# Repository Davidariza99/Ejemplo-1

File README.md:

# Proyecto embebidos (Pet_Sitting)

## Integrantes:

- David Ariza
- Andres Unibio
- Sharem Alonso

## Descripción:
Vigilante y cuidador de mascotas en casa, permite al usuario interactuar con su mascota a la distacia.

## Justificación: 
Se ha presentado un aumento significativo de la adopción de mascotas durante la pandemia, a medida que las personas vuelven a sus oficinas, universidades y demas obligaciones fuera del hogar, las mascotas que fueron criadas con la constante compañia de sus dueños, ahora sienten su ausencia. Este proyecto busca crear un nuevo vinculo entre el dueño y la mascota mientras este no se encuentre en casa

## Requerimientos funcionales:
- Vigilar 
- Comando de voz: Llamar, consentir, felicitar y corregir
- Movilidad (en un solo nivel)

## Requerimientos no funcionales:
- Cámara
- Audios pregrabados (mp3)
- Motor y alimentación
- Módulo WiFi
- Control remoto (desde un dispositivo móvil)

## Diagrama de bloques:
### Propuesto

### Final

## Proceso:
Ya teniendo definida la idea del proyecto, se procede a escoger cada uno de los elementos que nos permitirán realizar las tareas requeridas. Se pensó inicialmente en usar como módulo principal el ESP32, sin embargo, teniendo en cuenta el requerimiento de la cámara y que las referencias de cámara consultadas para usar en el ESP32 como la OV7670 tienen cierta complejidad al momento de configurarla y no ofrecen la mejor calidad, se decidió buscar otro módulo que contará con mejores especificaciones y facilitará el proceso. La ESP32 CAM cuenta con una cámara OV2460, que ofrece una mejor calidad y ya viene configurada a la placa.

Teniendo claro esto, lo siguiente era el desplazamiento ¿Cómo hace que esta ESP32 CAM se desplaze por el espacio para cumplir la labor de vigilancia? Se escogió un puente H (L293D) conectados a dos motores que le darán esa habilidad, además de montar la tarjeta en un servo motor para tener la capacidad también de mover la cámara. 

Ya cumpliendo con los primeros requerimiento de cámara y desplazamiento, el siguiente es el de la intereacción que se tendrá con la mascota. Para esto, la interacción mas viable es la de poder hablar con ellos, con nuestra propia voz, debido a esto se tuvieron variass opciones. Teniendo en cuenta las limitaciones de pines del ESP32 CAM no era posible conectar el amplificador y parlante para emitir los audios pregrabados, por lo que se optó por la opción de un esclavo.

La primera opción, que se puede observar en el primer diagrama de bloques propuesto, tenía como esclavo un microcontrolador con el DAC integrado, necesario para enviar las señales a un amplificador y después al parlante. Sin embargo, el chip del microcontrolador escogido ocupaba mucho espacio para las pocas conexiones que se pensaban hacer, además tampoco se contó con suficiento documentación para su funcionamiento.

Debido a lo anterior, se optó por el DFPlayer Mini un modulo reproductor de audio mp3 con amplificador integrado y que incluso puede funcionar por si solo simplemente conectando pulsadores. Por lo que se acomodaba muy bien a nuestras necesidades.

De esta manera se obtuvo el diagrama de bloques final, donde hay adicional un bloque nombrado "servidor" que es una configuración que se establece por software para poder controlar nuestro dispositivo de manera remota.

## Esquemático

El siquiente esquemático fue el realizado para la implementación, teniendo en cuenta las recomendaciones de conexión de por ejemplo el DFPlayer mini, que para recepción y emisión se agregaron unas resistencias en serie para eliminar el ruido. Para la entrada se agregó un regulador de tensión para asegurar a la salida una tensión de 5V que es lo necesario para alimentar nuestro circuito.

## PCB

La primera versión de la PCB se realizó sin tener en cuenta anchos de los caminos, lo cual es importante ya que si son muy delgados no funcionará correctamente el circuito, se necesitan caminos mas anchos para la transmisión de potencia y de información. También se puede observar que no se hizo uso de las vías en más capas, creando muchos caminos en formas no convenientes que pueden generar inductancias indeseadas.

### Versión 1

### Versión final

## Programación

Para realizar la programación de nuestro pet sitting, se hizo uso de la plataforma de arduino. Se hizo la siguiente conexión para poder programar nuestra ESP32 CAM:

de esta manera y descargando las librerías adecuadas, se puede acceder a un ejemplo de CameraWebServer, donde podemos observar el funcionamiento de la cámara, conenctándose remotamente desde un teléfono celular a una IP generada por el ESP32 CAM

Para luego hace las adiciones en el código de nuestros motores y el servomotor, teniendo nuestro programa listo para ser ejecutado por nuestra placa

El ejemplo además contaba con una interfaz gráfica que podíamos observar al momento de conectarnos a la IP, interfaz que se vió modificada, teniendo en cuenta nuestros requerimientos, agragando botones para el movimiento de motores y servo, además de deslizadores para controlar características de la cámara

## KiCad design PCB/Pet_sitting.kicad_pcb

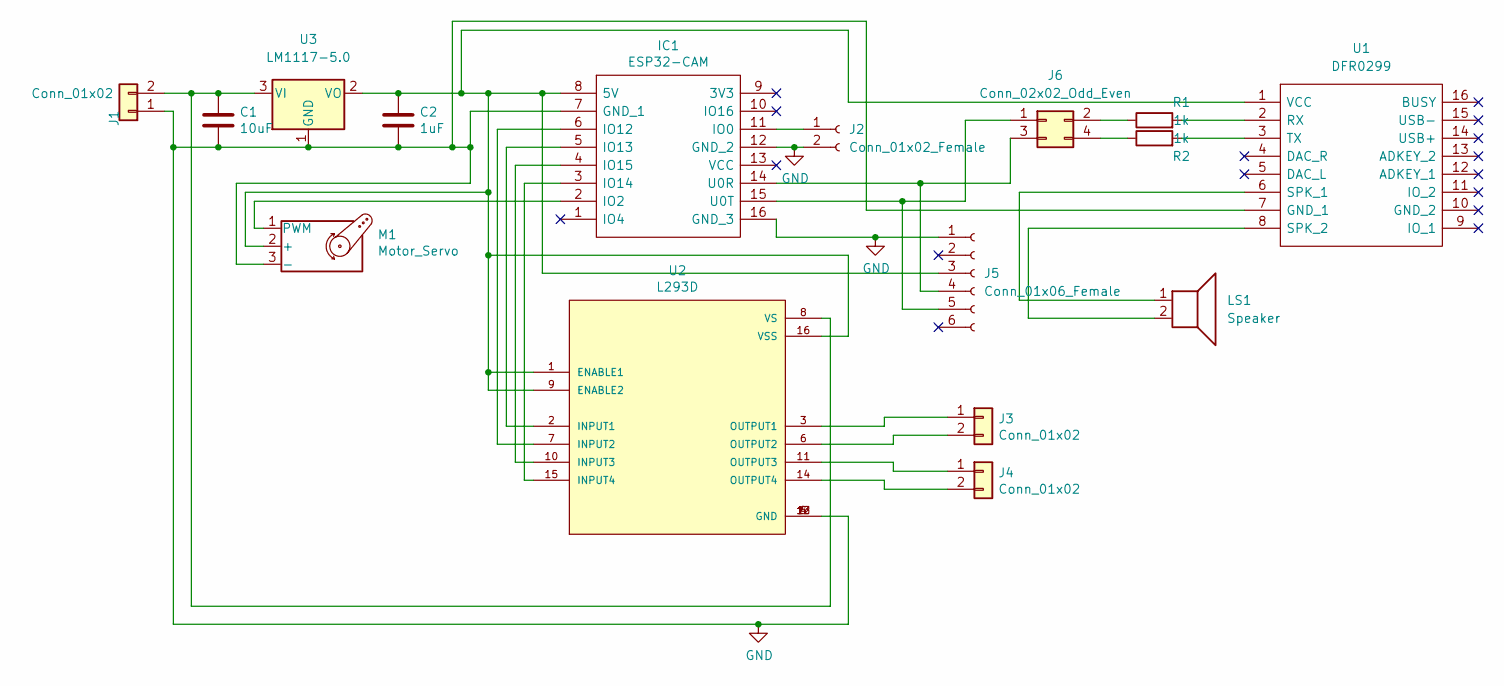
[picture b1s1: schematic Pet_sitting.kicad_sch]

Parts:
C1: 10uF; C_0805_2012Metric
C2: 1uF; C_0603_1608Metric
IC1: ESP32-CAM; ESP32CAM; Manufacturer_Part_Number ESP32-CAM
J1, J3, J4: Conn_01x02; PinHeader_1x02_P2.54mm_Vertical
J2: Conn_01x02_Female; PinSocket_1x02_P2.54mm_Vertical
J5: Conn_01x06_Female; PinSocket_1x06_P2.54mm_Vertical
J6: Conn_02x02_Odd_Even; PinHeader_2x02_P2.54mm_Vertical
LS1: Speaker; SolderWire-0.1sqmm_1x02_P3.6mm_D0.4mm_OD1mm
M1: Motor_Servo; PinHeader_1x03_P2.54mm_Vertical
R1, R2: 1k; R_Axial_DIN0204_L3.6mm_D1.6mm_P5.08mm_Horizontal
U1: DFR0299; DIPS1778W50P254L2100H170Q16N; Manufacturer_Part_Number DFR0299; Mouser Part Number 426-DFR0299
U2: L293D; DIP880W50P254L2000H510Q16
U3: LM1117-5.0; TO254P470X1016X2222-3P

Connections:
GND: C1.2, C2.2, IC1.7 (GND_1), IC1.12 (GND_2), IC1.16 (GND_3), J1.1, J2.2, J5.1, M1.3 (-), U1.7 (GND_1), U2.4 (GND), U2.5 (GND), U2.12 (GND), U2.13 (GND), U3.1 (GND)
unnamed: C1.1, J1.2, U2.8 (VS), U3.3 (VI)
unnamed: C2.1, IC1.8 (5V), J5.3, M1.2 (+), U1.1 (VCC), U2.1 (ENABLE1), U2.9 (ENABLE2), U2.16 (VSS), U3.2 (VO)
unnamed: IC1.2 (IO2), M1.1 (PWM)
unnamed: IC1.3 (IO14), U2.15 (INPUT4)
unnamed: IC1.4 (IO15), U2.10 (INPUT3)
unnamed: IC1.5 (IO13), U2.2 (INPUT1)
unnamed: IC1.6 (IO12), U2.7 (INPUT2)
unnamed: IC1.11 (IO0), J2.1
unnamed: IC1.14 (U0R), J5.4, J6.3
unnamed: IC1.15 (U0T), J5.5, J6.1
unnamed: J3.1, U2.3 (OUTPUT1)
unnamed: J3.2, U2.6 (OUTPUT2)
unnamed: J4.1, U2.11 (OUTPUT3)
unnamed: J4.2, U2.14 (OUTPUT4)
unnamed 15: LS1.1, U1.6 (SPK_1); also elsewhere on the board
unnamed 16: LS1.2, U1.8 (SPK_2); also elsewhere on the board
unnamed: J6.2, R1.1
unnamed: J6.4, R2.1
unnamed: R1.2, U1.2 (RX)
unnamed: R2.2, U1.3 (TX)

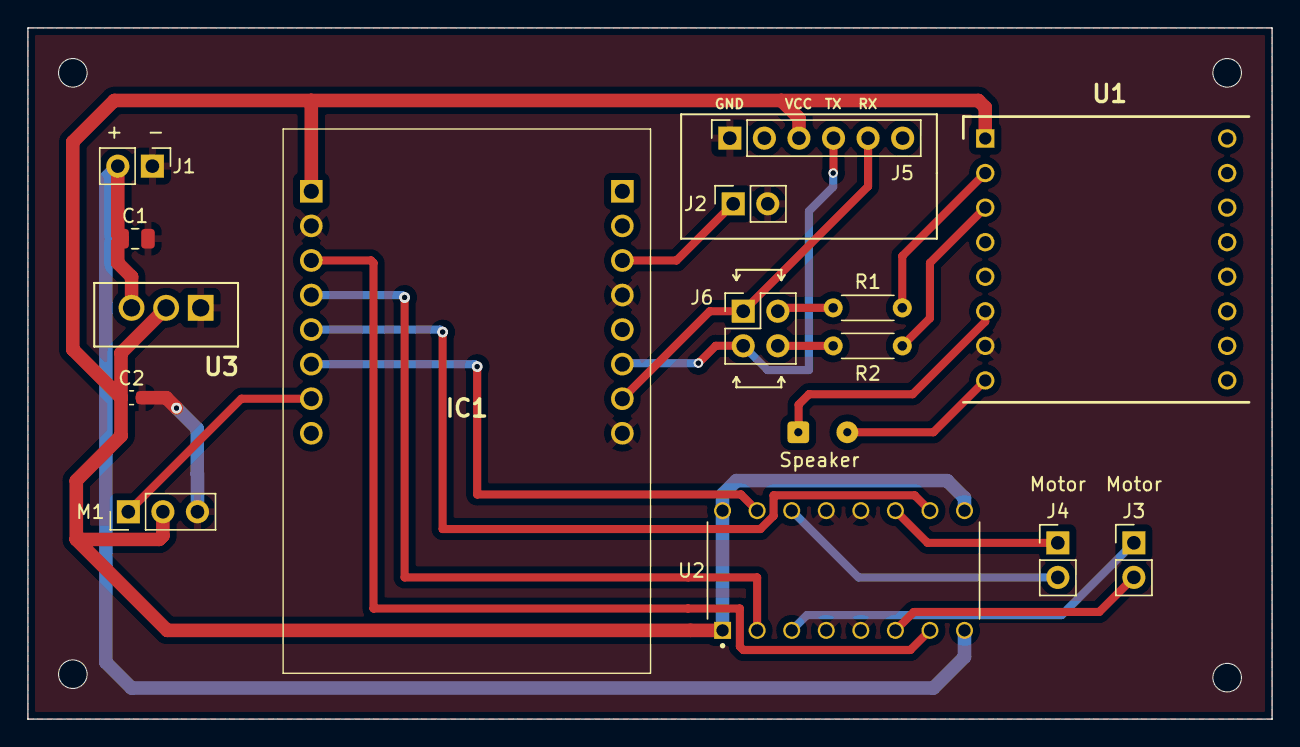
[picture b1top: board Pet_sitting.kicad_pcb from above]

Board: 2 copper layers, 91.4 x 50.8 mm, 16 parts (0 on the bottom side), 21 nets.

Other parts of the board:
Speaker: Speaker; SolderWire-0.1sqmm_1x02_P3.6mm_D0.4mm_OD1mm

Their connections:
unnamed 15: Speaker.1; also elsewhere on the board
unnamed 16: Speaker.2; also elsewhere on the board

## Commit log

2021-10-26 Added Diagrama_bloques.drawio
2022-01-17 Agrego datasheets
2022-01-17 Diagrama_bloques_V2.png
2022-01-17 Added Diagrama_bloques_V2.png
2022-02-01 Rename README.md to imagenes/README.md
